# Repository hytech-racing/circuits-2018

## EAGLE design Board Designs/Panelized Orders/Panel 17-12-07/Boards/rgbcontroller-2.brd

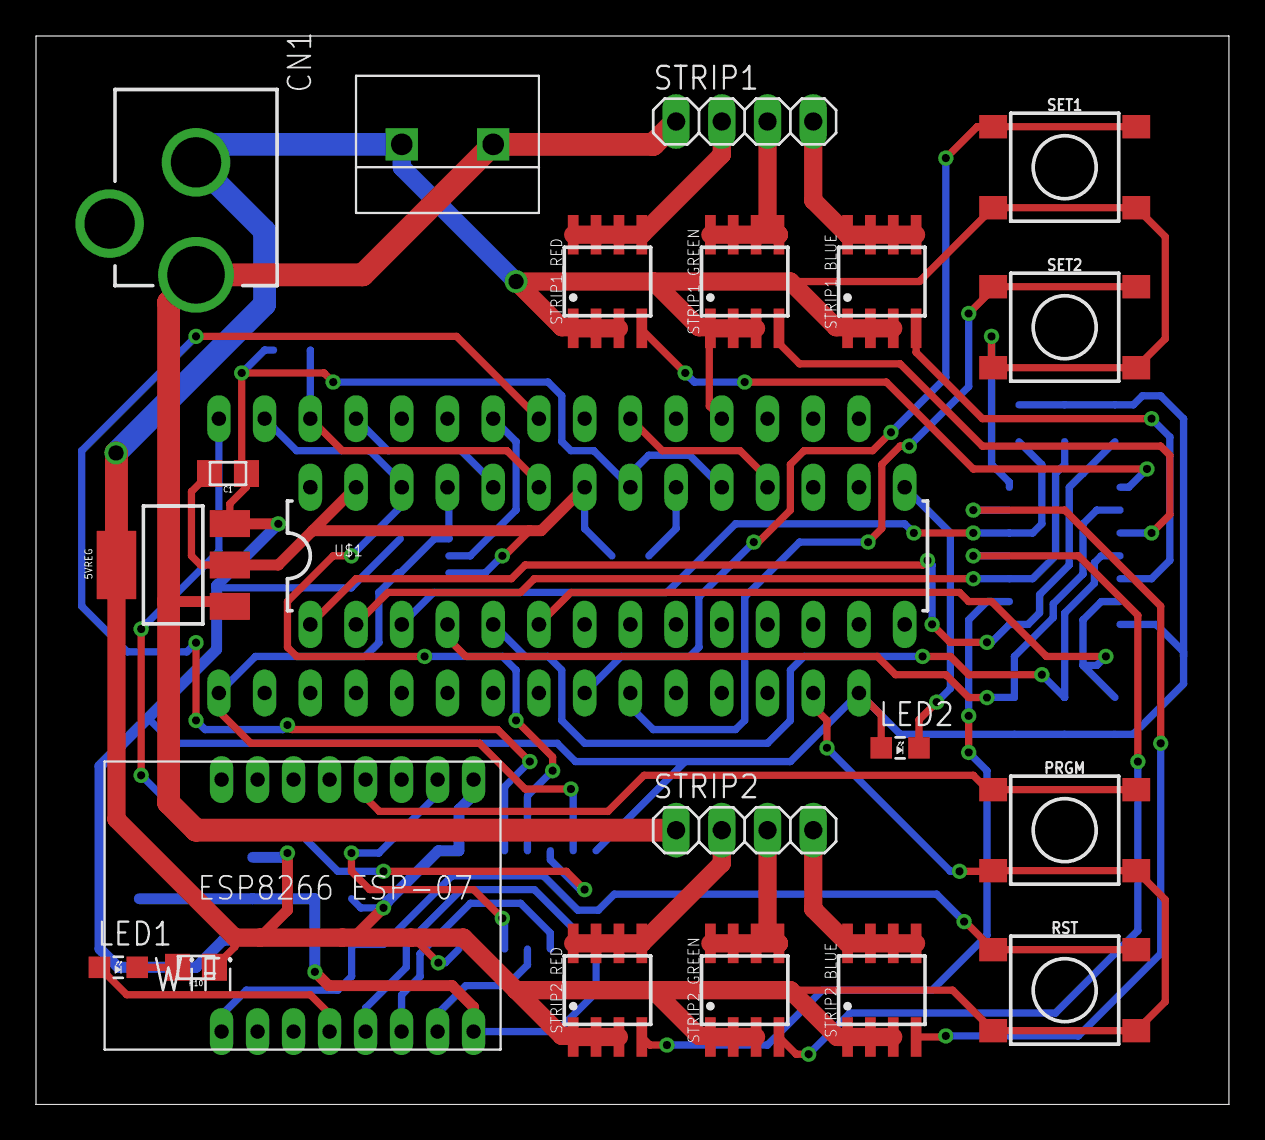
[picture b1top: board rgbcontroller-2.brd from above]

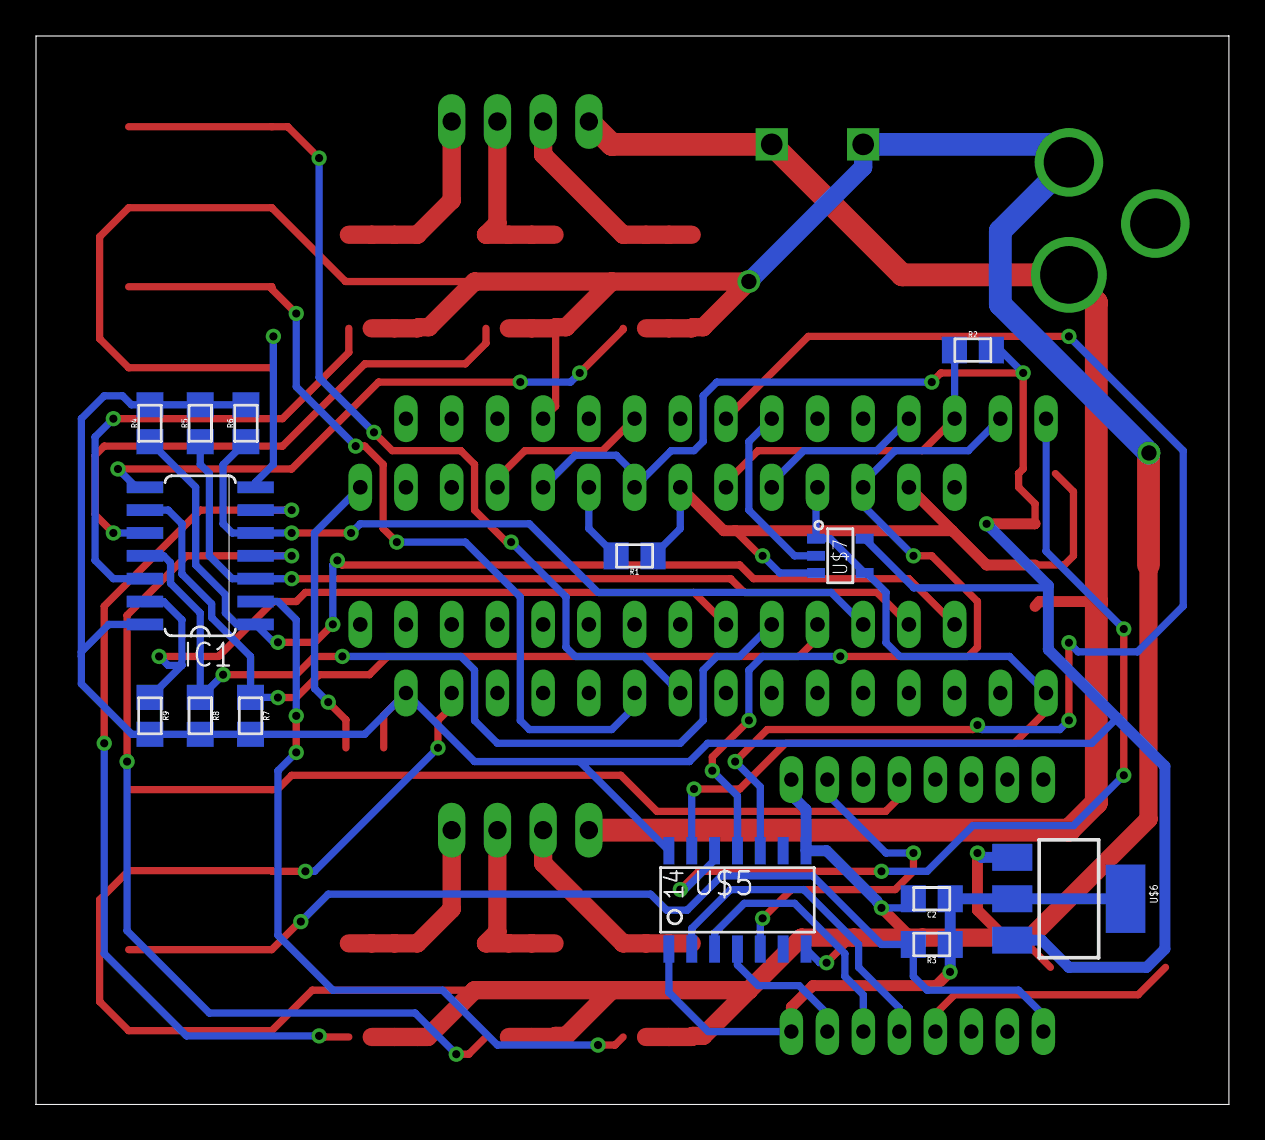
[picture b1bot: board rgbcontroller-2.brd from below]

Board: 2 copper layers, 66.3 x 59.4 mm, 36 parts (14 on the bottom side), 42 nets.

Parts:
5VREG: SOT223
C1: .1µF; 0805
C2: 1µF; 0805
CN1: DCJACK_2MM_PTH
IC1: 74HC04D; SO14
LED1: Red; LED-805
LED2: LED-805
PRGM: TACTILE_SWITCH_SMD_6.2MM_TALL
R1: 2.2k; 0805
R2, R3, R4, R5, R6, R7, R8, R9: 10k; 0805
R10: 100; 0805
RST: TACTILE_SWITCH_SMD_6.2MM_TALL
SET1, SET2: TACTILE_SWITCH_SMD_6.2MM_TALL
STRIP1, STRIP2: 1X04
STRIP1_BLUE, STRIP1_GREEN, STRIP1_RED, STRIP2_BLUE, STRIP2_GREEN, STRIP2_RED: MDS1656; SOIC-08
U$1: TLC5940; DIL28-3
U$2: ARDUINO_NANO
U$3: TERMINAL_BLOCK_DG301-02P; DG301-02P
U$4: ESP8266_ESP-07
U$5: SOIC-14
U$6: TLV1117LV33; SOT223
U$7: SN74LVC1G08; SOT-23-5

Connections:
+3V3: C2.1, R3.1, U$4.P$8, U$5.1, U$6.2, U$6.4
+5V: 5VREG.3, C1.1, IC1.14, LED2.A, R2.2, R4.2, R5.2, R6.2, R7.2, R8.2, R9.2, U$1.19, U$1.21, U$2.VIN, U$5.14, U$6.3, U$7.5
+12V: 5VREG.1, CN1.PWR, STRIP1.1, STRIP2.1, U$3.1
BLANK: R2.1, U$1.23, U$2.D10
GND: 5VREG.2, 5VREG.4, C1.2, C2.2, CN1.GND, IC1.7, PRGM.A1, PRGM.A2, R1.1, R10.1, RST.A1, RST.A2, SET1.A1, SET1.A2, SET2.A1, SET2.A2, STRIP1_BLUE.1, STRIP1_BLUE.2, STRIP1_BLUE.3, STRIP1_GREEN.1, STRIP1_GREEN.2, STRIP1_GREEN.3, STRIP1_RED.1, STRIP1_RED.2, STRIP1_RED.3, STRIP2_BLUE.1, STRIP2_BLUE.2, STRIP2_BLUE.3, STRIP2_GREEN.1, STRIP2_GREEN.2, STRIP2_GREEN.3, STRIP2_RED.1, STRIP2_RED.2, STRIP2_RED.3, U$1.22, U$1.27, U$2.GND, U$2.GND1, U$3.2, U$4.P$9, U$5.7, U$5.8, U$6.1, U$7.3
MISO: U$2.D12, U$5.12
MISO_33: U$4.P$6, U$5.3
MOSI: U$1.26, U$2.D11, U$5.11
MOSI_33: U$4.P$7, U$5.4
unnamed: STRIP2.2, STRIP2_RED.5, STRIP2_RED.6, STRIP2_RED.7, STRIP2_RED.8
unnamed: STRIP1.2, STRIP1_RED.5, STRIP1_RED.6, STRIP1_RED.7, STRIP1_RED.8
unnamed: IC1.2, STRIP2_RED.4
unnamed: IC1.4, STRIP2_GREEN.4
unnamed: PRGM.B1, PRGM.B2, U$4.P$12
unnamed: R1.2, U$1.20
unnamed: U$1.18, U$2.D3
unnamed: LED1.A, U$4.P$4
unnamed: IC1.8, STRIP1_RED.4
unnamed: IC1.10, STRIP1_GREEN.4
unnamed: IC1.12, STRIP1_BLUE.4
unnamed: IC1.6, STRIP2_BLUE.4
unnamed: IC1.1, R4.1, U$1.1
unnamed: IC1.3, R5.1, U$1.2
unnamed: STRIP1.3, STRIP1_GREEN.5, STRIP1_GREEN.6, STRIP1_GREEN.7, STRIP1_GREEN.8
unnamed: STRIP1.4, STRIP1_BLUE.5, STRIP1_BLUE.6, STRIP1_BLUE.7, STRIP1_BLUE.8
unnamed: STRIP2.3, STRIP2_GREEN.5, STRIP2_GREEN.6, STRIP2_GREEN.7, STRIP2_GREEN.8
unnamed: STRIP2.4, STRIP2_BLUE.5, STRIP2_BLUE.6, STRIP2_BLUE.7, STRIP2_BLUE.8
unnamed: IC1.5, R6.1, U$1.3
unnamed: IC1.13, R9.1, U$1.6
unnamed: R3.2, RST.B1, RST.B2, U$4.P$1
unnamed: IC1.11, R8.1, U$1.5
unnamed: IC1.9, R7.1, U$1.4
unnamed: LED2.C, U$1.15
unnamed: LED1.C, R10.2
SCK: U$1.25, U$2.D13, U$5.13, U$7.1, U$7.4
SCK_33: U$4.P$5, U$5.2
SET1: SET1.B1, SET1.B2, U$2.A5
SET2: SET2.B1, SET2.B2, U$2.A6
SS_ESP8266: U$2.D5, U$5.10
SS_ESP8266_33: U$4.P$10, U$5.5
SS_TLC5940: U$2.D6, U$7.2
XLAT: U$1.24, U$2.D9

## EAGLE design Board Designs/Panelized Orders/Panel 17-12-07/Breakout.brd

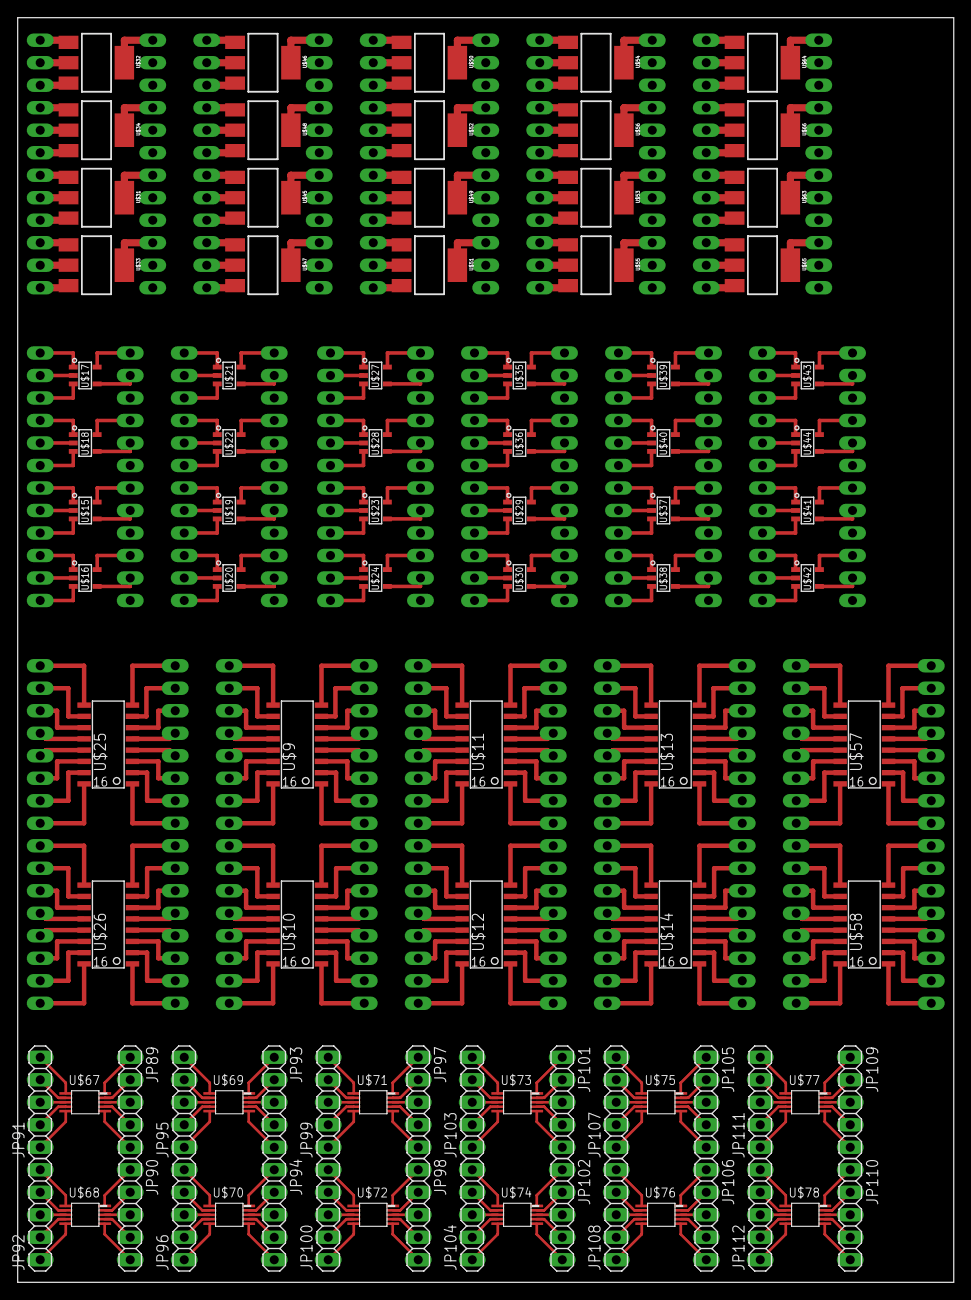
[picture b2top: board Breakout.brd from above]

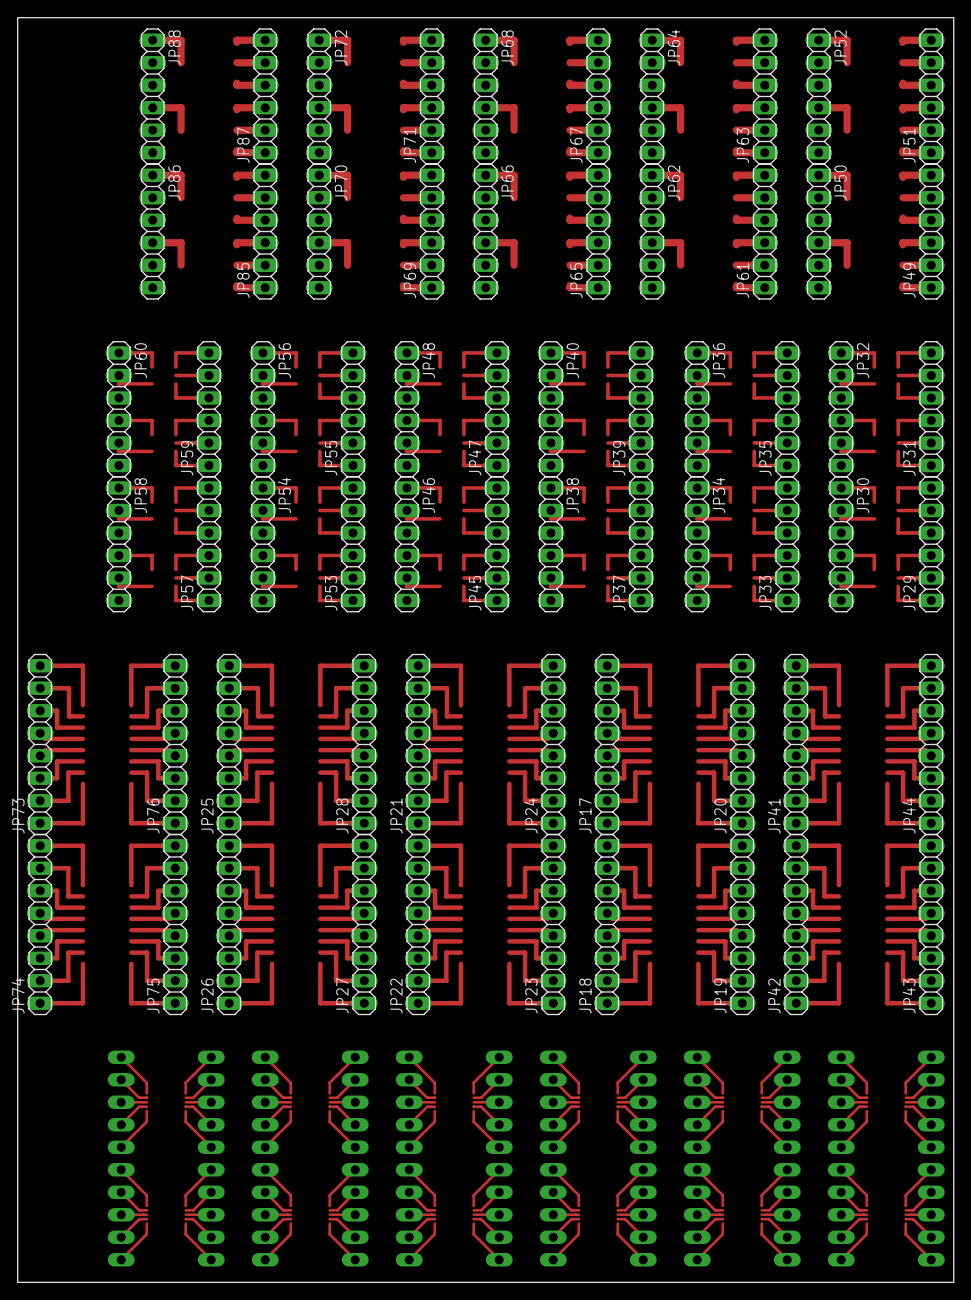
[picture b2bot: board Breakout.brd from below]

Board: 2 copper layers, 105.7 x 142.7 mm, 154 parts (64 on the bottom side), 480 nets.

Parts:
JP17, JP18, JP19, JP20, JP21, JP22, JP23, JP24, JP25, JP26, JP27, JP28, JP41, JP42, JP43, JP44, JP73, JP74, JP75, JP76: 1X08
JP29, JP30, JP31, JP32, JP33, JP34, JP35, JP36, JP37, JP38, JP39, JP40, JP45, JP46, JP47, JP48, JP49, JP50, JP51, JP52, JP53, JP54, JP55, JP56, JP57, JP58, JP59, JP60, JP61, JP62, JP63, JP64, JP65, JP66, JP67, JP68, JP69, JP70, JP71, JP72, JP85, JP86, JP87, JP88: 1X06
JP89, JP90, JP91, JP92, JP93, JP94, JP95, JP96, JP97, JP98, JP99, JP100, JP101, JP102, JP103, JP104, JP105, JP106, JP107, JP108, JP109, JP110, JP111, JP112: 1X05
U$9, U$10, U$11, U$12, U$13, U$14, U$25, U$26, U$57, U$58: SOIC16; SOIC-16
U$15, U$17, U$19, U$21, U$23, U$27, U$29, U$35, U$37, U$39, U$41, U$43: SN74LVC1G06; SOT-23-5
U$16, U$18, U$20, U$22, U$24, U$28, U$30, U$36, U$38, U$40, U$42, U$44: SN74LVC1G07; SOT-23-5
U$31, U$32, U$33, U$34, U$45, U$46, U$47, U$48, U$49, U$50, U$51, U$52, U$53, U$54, U$55, U$56, U$63, U$64, U$65, U$66: SOT223
U$67, U$68, U$69, U$70, U$71, U$72, U$73, U$74, U$75, U$76, U$77, U$78: INA226; VSSOP-10

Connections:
unnamed: JP17.1, U$9.1
unnamed: JP17.2, U$9.2
unnamed: JP17.3, U$9.3
unnamed: JP17.4, U$9.4
unnamed: JP17.5, U$9.5
unnamed: JP17.6, U$9.6
unnamed: JP17.7, U$9.7
unnamed: JP17.8, U$9.8
unnamed: JP18.1, U$10.1
unnamed: JP18.2, U$10.2
unnamed: JP18.3, U$10.3
unnamed: JP18.4, U$10.4
unnamed: JP18.5, U$10.5
unnamed: JP18.6, U$10.6
unnamed: JP18.7, U$10.7
unnamed: JP18.8, U$10.8
unnamed: JP19.1, U$10.16
unnamed: JP19.2, U$10.15
unnamed: JP19.3, U$10.14
unnamed: JP19.4, U$10.13
unnamed: JP19.5, U$10.12
unnamed: JP19.6, U$10.11
unnamed: JP19.7, U$10.10
unnamed: JP19.8, U$10.9
unnamed: JP20.1, U$9.16
unnamed: JP20.2, U$9.15
unnamed: JP20.3, U$9.14
unnamed: JP20.4, U$9.13
unnamed: JP20.5, U$9.12
unnamed: JP20.6, U$9.11
unnamed: JP20.7, U$9.10
unnamed: JP20.8, U$9.9
unnamed: JP21.1, U$11.1
unnamed: JP21.2, U$11.2
unnamed: JP21.3, U$11.3
unnamed: JP21.4, U$11.4
unnamed: JP21.5, U$11.5
unnamed: JP21.6, U$11.6
unnamed: JP21.7, U$11.7
unnamed: JP21.8, U$11.8
unnamed: JP22.1, U$12.1
unnamed: JP22.2, U$12.2
unnamed: JP22.3, U$12.3
unnamed: JP22.4, U$12.4
unnamed: JP22.5, U$12.5
unnamed: JP22.6, U$12.6
unnamed: JP22.7, U$12.7
unnamed: JP22.8, U$12.8
unnamed: JP23.1, U$12.16
unnamed: JP23.2, U$12.15
unnamed: JP23.3, U$12.14
unnamed: JP23.4, U$12.13
unnamed: JP23.5, U$12.12
unnamed: JP23.6, U$12.11
unnamed: JP23.7, U$12.10
unnamed: JP23.8, U$12.9
unnamed: JP24.1, U$11.16
unnamed: JP24.2, U$11.15
unnamed: JP24.3, U$11.14
unnamed: JP24.4, U$11.13
unnamed: JP24.5, U$11.12
unnamed: JP24.6, U$11.11
unnamed: JP24.7, U$11.10
unnamed: JP24.8, U$11.9
unnamed: JP25.1, U$13.1
unnamed: JP25.2, U$13.2
unnamed: JP25.3, U$13.3
unnamed: JP25.4, U$13.4
unnamed: JP25.5, U$13.5
unnamed: JP25.6, U$13.6
unnamed: JP25.7, U$13.7
unnamed: JP25.8, U$13.8
unnamed: JP26.1, U$14.1
unnamed: JP26.2, U$14.2
unnamed: JP26.3, U$14.3
unnamed: JP26.4, U$14.4
unnamed: JP26.5, U$14.5
unnamed: JP26.6, U$14.6
unnamed: JP26.7, U$14.7
unnamed: JP26.8, U$14.8
unnamed: JP27.1, U$14.16
unnamed: JP27.2, U$14.15
unnamed: JP27.3, U$14.14
unnamed: JP27.4, U$14.13
unnamed: JP27.5, U$14.12
unnamed: JP27.6, U$14.11
unnamed: JP27.7, U$14.10
unnamed: JP27.8, U$14.9
unnamed: JP28.1, U$13.16
unnamed: JP28.2, U$13.15
unnamed: JP28.3, U$13.14
unnamed: JP28.4, U$13.13
unnamed: JP28.5, U$13.12
unnamed: JP28.6, U$13.11
unnamed: JP28.7, U$13.10
unnamed: JP28.8, U$13.9
unnamed: JP30.1, U$15.5
unnamed: JP30.2, U$15.4
unnamed: JP30.4, U$16.5
unnamed: JP30.5, U$16.4
unnamed: JP29.6, U$15.1
unnamed: JP29.5, U$15.2
unnamed: JP29.4, U$15.3
unnamed: JP29.3, U$16.1
unnamed: JP29.2, U$16.2
unnamed: JP29.1, U$16.3
unnamed: JP32.1, U$17.5
unnamed: JP32.2, U$17.4
unnamed: JP32.4, U$18.5
unnamed: JP32.5, U$18.4
unnamed: JP31.6, U$17.1
unnamed: JP31.5, U$17.2
unnamed: JP31.4, U$17.3
unnamed: JP31.3, U$18.1
unnamed: JP31.2, U$18.2
unnamed: JP31.1, U$18.3
unnamed: JP34.1, U$19.5
unnamed: JP34.2, U$19.4
unnamed: JP34.4, U$20.5
unnamed: JP34.5, U$20.4
unnamed: JP33.6, U$19.1
unnamed: JP33.5, U$19.2
unnamed: JP33.4, U$19.3
unnamed: JP33.3, U$20.1
unnamed: JP33.2, U$20.2
unnamed: JP33.1, U$20.3
unnamed: JP36.1, U$21.5
unnamed: JP36.2, U$21.4
unnamed: JP36.4, U$22.5
unnamed: JP36.5, U$22.4
unnamed: JP35.6, U$21.1
unnamed: JP35.5, U$21.2
unnamed: JP35.4, U$21.3
unnamed: JP35.3, U$22.1
unnamed: JP35.2, U$22.2
unnamed: JP35.1, U$22.3
unnamed: JP38.1, U$23.5
unnamed: JP38.2, U$23.4
unnamed: JP38.4, U$24.5
unnamed: JP38.5, U$24.4
unnamed: JP37.6, U$23.1
unnamed: JP37.5, U$23.2
unnamed: JP37.4, U$23.3
unnamed: JP37.3, U$24.1
unnamed: JP37.2, U$24.2
unnamed: JP37.1, U$24.3
unnamed: JP40.1, U$27.5
unnamed: JP40.2, U$27.4
unnamed: JP40.4, U$28.5
unnamed: JP40.5, U$28.4
unnamed: JP39.6, U$27.1
unnamed: JP39.5, U$27.2
unnamed: JP39.4, U$27.3
unnamed: JP39.3, U$28.1
unnamed: JP39.2, U$28.2
unnamed: JP39.1, U$28.3
unnamed: JP46.1, U$29.5
unnamed: JP46.2, U$29.4
unnamed: JP46.4, U$30.5
unnamed: JP46.5, U$30.4
unnamed: JP45.6, U$29.1
unnamed: JP45.5, U$29.2
unnamed: JP45.4, U$29.3
unnamed: JP45.3, U$30.1
unnamed: JP41.1, U$25.1
unnamed: JP41.2, U$25.2
unnamed: JP41.3, U$25.3
unnamed: JP41.4, U$25.4
unnamed: JP41.5, U$25.5
unnamed: JP41.6, U$25.6
unnamed: JP41.7, U$25.7
unnamed: JP41.8, U$25.8
unnamed: JP42.1, U$26.1
unnamed: JP42.2, U$26.2
unnamed: JP42.3, U$26.3
unnamed: JP42.4, U$26.4
unnamed: JP42.5, U$26.5
unnamed: JP42.6, U$26.6
unnamed: JP42.7, U$26.7
unnamed: JP42.8, U$26.8
unnamed: JP43.1, U$26.16
unnamed: JP43.2, U$26.15
unnamed: JP43.3, U$26.14
unnamed: JP43.4, U$26.13
unnamed: JP43.5, U$26.12
unnamed: JP43.6, U$26.11
unnamed: JP43.7, U$26.10
unnamed: JP43.8, U$26.9
unnamed: JP44.1, U$25.16
unnamed: JP44.2, U$25.15
unnamed: JP44.3, U$25.14
unnamed: JP44.4, U$25.13
unnamed: JP44.5, U$25.12
unnamed: JP44.6, U$25.11
unnamed: JP44.7, U$25.10
unnamed: JP44.8, U$25.9
unnamed: JP45.2, U$30.2
unnamed: JP45.1, U$30.3
unnamed: JP48.1, U$35.5
unnamed: JP48.2, U$35.4
unnamed: JP48.4, U$36.5
unnamed: JP48.5, U$36.4
unnamed: JP47.6, U$35.1
unnamed: JP47.5, U$35.2
unnamed: JP47.4, U$35.3
unnamed: JP47.3, U$36.1
unnamed: JP47.2, U$36.2
unnamed: JP47.1, U$36.3
unnamed: JP54.1, U$37.5
unnamed: JP54.2, U$37.4
unnamed: JP54.4, U$38.5
unnamed: JP54.5, U$38.4
unnamed: JP53.6, U$37.1
unnamed: JP53.5, U$37.2
unnamed: JP53.4, U$37.3
unnamed: JP53.3, U$38.1
unnamed: JP50.1, U$31.4
unnamed: JP49.6, U$31.1
unnamed: JP49.5, U$31.2
unnamed: JP49.4, U$31.3
unnamed: JP49.3, U$33.1
unnamed: JP49.2, U$33.2
unnamed: JP49.1, U$33.3
unnamed: JP50.4, U$33.4
unnamed: JP52.1, U$32.4
unnamed: JP52.4, U$34.4
unnamed: JP51.6, U$32.1
unnamed: JP51.5, U$32.2
unnamed: JP51.4, U$32.3
unnamed: JP51.3, U$34.1
unnamed: JP51.2, U$34.2
unnamed: JP51.1, U$34.3
unnamed: JP53.2, U$38.2
unnamed: JP53.1, U$38.3
unnamed: JP56.1, U$39.5
unnamed: JP56.2, U$39.4
unnamed: JP56.4, U$40.5
unnamed: JP56.5, U$40.4
unnamed: JP55.6, U$39.1
unnamed: JP55.5, U$39.2
unnamed: JP55.4, U$39.3
unnamed: JP55.3, U$40.1
unnamed: JP55.2, U$40.2
unnamed: JP55.1, U$40.3
unnamed: JP58.1, U$41.5
unnamed: JP58.2, U$41.4
unnamed: JP58.4, U$42.5
unnamed: JP58.5, U$42.4
unnamed: JP57.6, U$41.1
unnamed: JP57.5, U$41.2
unnamed: JP57.4, U$41.3
unnamed: JP57.3, U$42.1
unnamed: JP57.2, U$42.2
unnamed: JP57.1, U$42.3
unnamed: JP60.1, U$43.5
unnamed: JP60.2, U$43.4
unnamed: JP60.4, U$44.5
unnamed: JP60.5, U$44.4
unnamed: JP59.6, U$43.1
unnamed: JP59.5, U$43.2
unnamed: JP59.4, U$43.3
unnamed: JP59.3, U$44.1
unnamed: JP59.2, U$44.2
unnamed: JP59.1, U$44.3
unnamed: JP62.1, U$45.4
unnamed: JP61.6, U$45.1
unnamed: JP61.5, U$45.2
unnamed: JP61.4, U$45.3
unnamed: JP61.3, U$47.1
unnamed: JP61.2, U$47.2
unnamed: JP61.1, U$47.3
unnamed: JP62.4, U$47.4
unnamed: JP64.1, U$46.4
unnamed: JP64.4, U$48.4
unnamed: JP63.6, U$46.1
unnamed: JP63.5, U$46.2
unnamed: JP63.4, U$46.3
unnamed: JP63.3, U$48.1
unnamed: JP63.2, U$48.2
unnamed: JP63.1, U$48.3
unnamed: JP66.1, U$49.4
unnamed: JP65.6, U$49.1
unnamed: JP65.5, U$49.2
unnamed: JP65.4, U$49.3
unnamed: JP65.3, U$51.1
unnamed: JP65.2, U$51.2
unnamed: JP65.1, U$51.3
unnamed: JP66.4, U$51.4
unnamed: JP68.1, U$50.4
unnamed: JP68.4, U$52.4
unnamed: JP67.6, U$50.1
unnamed: JP67.5, U$50.2
unnamed: JP67.4, U$50.3
unnamed: JP67.3, U$52.1
unnamed: JP67.2, U$52.2
unnamed: JP67.1, U$52.3
unnamed: JP70.1, U$53.4
unnamed: JP69.6, U$53.1
unnamed: JP69.5, U$53.2
unnamed: JP69.4, U$53.3
unnamed: JP69.3, U$55.1
unnamed: JP69.2, U$55.2
unnamed: JP69.1, U$55.3
unnamed: JP70.4, U$55.4
unnamed: JP72.1, U$54.4
unnamed: JP72.4, U$56.4
unnamed: JP71.6, U$54.1
unnamed: JP71.5, U$54.2
unnamed: JP71.4, U$54.3
unnamed: JP71.3, U$56.1
unnamed: JP71.2, U$56.2
unnamed: JP71.1, U$56.3
unnamed: JP73.1, U$57.1
unnamed: JP73.2, U$57.2
unnamed: JP73.3, U$57.3
unnamed: JP73.4, U$57.4
unnamed: JP73.5, U$57.5
unnamed: JP73.6, U$57.6
unnamed: JP73.7, U$57.7
unnamed: JP73.8, U$57.8
unnamed: JP74.1, U$58.1
unnamed: JP74.2, U$58.2
unnamed: JP74.3, U$58.3
unnamed: JP74.4, U$58.4
unnamed: JP74.5, U$58.5
unnamed: JP74.6, U$58.6
unnamed: JP74.7, U$58.7
unnamed: JP74.8, U$58.8
unnamed: JP75.1, U$58.16
unnamed: JP75.2, U$58.15
unnamed: JP75.3, U$58.14
unnamed: JP75.4, U$58.13
unnamed: JP75.5, U$58.12
unnamed: JP75.6, U$58.11
unnamed: JP75.7, U$58.10
unnamed: JP75.8, U$58.9
unnamed: JP76.1, U$57.16
unnamed: JP76.2, U$57.15
unnamed: JP76.3, U$57.14
unnamed: JP76.4, U$57.13
unnamed: JP76.5, U$57.12
unnamed: JP76.6, U$57.11
unnamed: JP76.7, U$57.10
unnamed: JP76.8, U$57.9
unnamed: JP86.1, U$63.4
unnamed: JP85.6, U$63.1
unnamed: JP85.5, U$63.2
unnamed: JP85.4, U$63.3
unnamed: JP85.3, U$65.1
unnamed: JP85.2, U$65.2
unnamed: JP85.1, U$65.3
unnamed: JP86.4, U$65.4
unnamed: JP88.1, U$64.4
unnamed: JP88.4, U$66.4
unnamed: JP87.6, U$64.1
unnamed: JP87.5, U$64.2
unnamed: JP87.4, U$64.3
unnamed: JP87.3, U$66.1
unnamed: JP87.2, U$66.2
unnamed: JP87.1, U$66.3
unnamed: JP92.1, U$68.5
unnamed: JP92.2, U$68.4
unnamed: JP92.3, U$68.3
unnamed: JP92.4, U$68.2
unnamed: JP92.5, U$68.1
unnamed: JP91.1, U$67.5
unnamed: JP91.2, U$67.4
unnamed: JP91.3, U$67.3
unnamed: JP91.4, U$67.2
unnamed: JP91.5, U$67.1
unnamed: JP90.1, U$68.10
unnamed: JP90.2, U$68.9
unnamed: JP90.3, U$68.8
unnamed: JP90.4, U$68.7
unnamed: JP90.5, U$68.6
unnamed: JP89.1, U$67.10
unnamed: JP89.2, U$67.9
unnamed: JP89.3, U$67.8
unnamed: JP89.4, U$67.7
unnamed: JP89.5, U$67.6
unnamed: JP96.1, U$70.5
unnamed: JP96.2, U$70.4
unnamed: JP96.3, U$70.3
unnamed: JP96.4, U$70.2
unnamed: JP96.5, U$70.1
unnamed: JP95.1, U$69.5
unnamed: JP95.2, U$69.4
unnamed: JP95.3, U$69.3
unnamed: JP95.4, U$69.2
unnamed: JP95.5, U$69.1
unnamed: JP94.1, U$70.10
unnamed: JP94.2, U$70.9
unnamed: JP94.3, U$70.8
unnamed: JP94.4, U$70.7
unnamed: JP94.5, U$70.6
unnamed: JP93.1, U$69.10
unnamed: JP93.2, U$69.9
unnamed: JP93.3, U$69.8
unnamed: JP93.4, U$69.7
unnamed: JP93.5, U$69.6
unnamed: JP100.1, U$72.5
unnamed: JP100.2, U$72.4
unnamed: JP100.3, U$72.3
unnamed: JP100.4, U$72.2
unnamed: JP100.5, U$72.1
unnamed: JP99.1, U$71.5
unnamed: JP99.2, U$71.4
unnamed: JP99.3, U$71.3
unnamed: JP99.4, U$71.2
unnamed: JP99.5, U$71.1
unnamed: JP98.1, U$72.10
unnamed: JP98.2, U$72.9
unnamed: JP98.3, U$72.8
unnamed: JP98.4, U$72.7
unnamed: JP98.5, U$72.6
unnamed: JP97.1, U$71.10
unnamed: JP97.2, U$71.9
unnamed: JP97.3, U$71.8
unnamed: JP97.4, U$71.7
unnamed: JP97.5, U$71.6
unnamed: JP104.1, U$74.5
unnamed: JP104.2, U$74.4
unnamed: JP104.3, U$74.3
unnamed: JP104.4, U$74.2
unnamed: JP104.5, U$74.1
unnamed: JP103.1, U$73.5
unnamed: JP103.2, U$73.4
unnamed: JP103.3, U$73.3
unnamed: JP103.4, U$73.2
unnamed: JP103.5, U$73.1
unnamed: JP102.1, U$74.10
unnamed: JP102.2, U$74.9
unnamed: JP102.3, U$74.8
unnamed: JP102.4, U$74.7
unnamed: JP102.5, U$74.6
unnamed: JP101.1, U$73.10
unnamed: JP101.2, U$73.9
unnamed: JP101.3, U$73.8
unnamed: JP101.4, U$73.7
unnamed: JP101.5, U$73.6
unnamed: JP108.1, U$76.5
unnamed: JP108.2, U$76.4
unnamed: JP108.3, U$76.3
unnamed: JP108.4, U$76.2
unnamed: JP108.5, U$76.1
unnamed: JP107.1, U$75.5
unnamed: JP107.2, U$75.4
unnamed: JP107.3, U$75.3
unnamed: JP107.4, U$75.2
unnamed: JP107.5, U$75.1
unnamed: JP106.1, U$76.10
unnamed: JP106.2, U$76.9
unnamed: JP106.3, U$76.8
unnamed: JP106.4, U$76.7
unnamed: JP106.5, U$76.6
unnamed: JP105.1, U$75.10
unnamed: JP105.2, U$75.9
unnamed: JP105.3, U$75.8
unnamed: JP105.4, U$75.7
unnamed: JP105.5, U$75.6
unnamed: JP112.1, U$78.5
unnamed: JP112.2, U$78.4
unnamed: JP112.3, U$78.3
unnamed: JP112.4, U$78.2
unnamed: JP112.5, U$78.1
unnamed: JP111.1, U$77.5
unnamed: JP111.2, U$77.4
unnamed: JP111.3, U$77.3
unnamed: JP111.4, U$77.2
unnamed: JP111.5, U$77.1
unnamed: JP110.1, U$78.10
unnamed: JP110.2, U$78.9
unnamed: JP110.3, U$78.8
unnamed: JP110.4, U$78.7
unnamed: JP110.5, U$78.6
unnamed: JP109.1, U$77.10
unnamed: JP109.2, U$77.9
unnamed: JP109.3, U$77.8
unnamed: JP109.4, U$77.7
unnamed: JP109.5, U$77.6

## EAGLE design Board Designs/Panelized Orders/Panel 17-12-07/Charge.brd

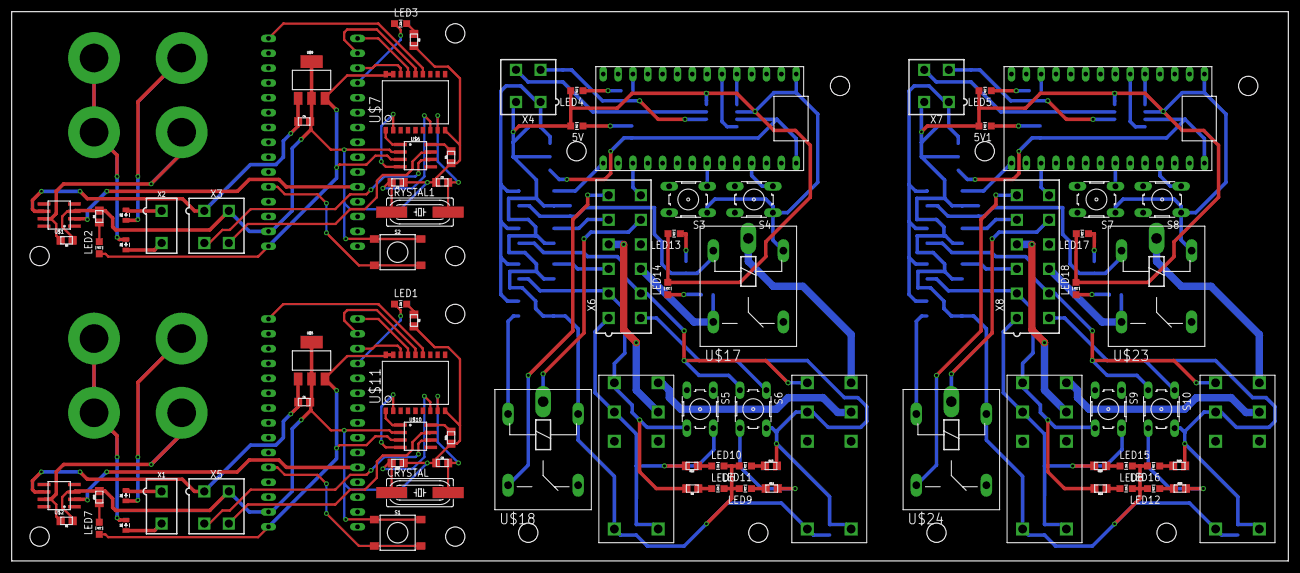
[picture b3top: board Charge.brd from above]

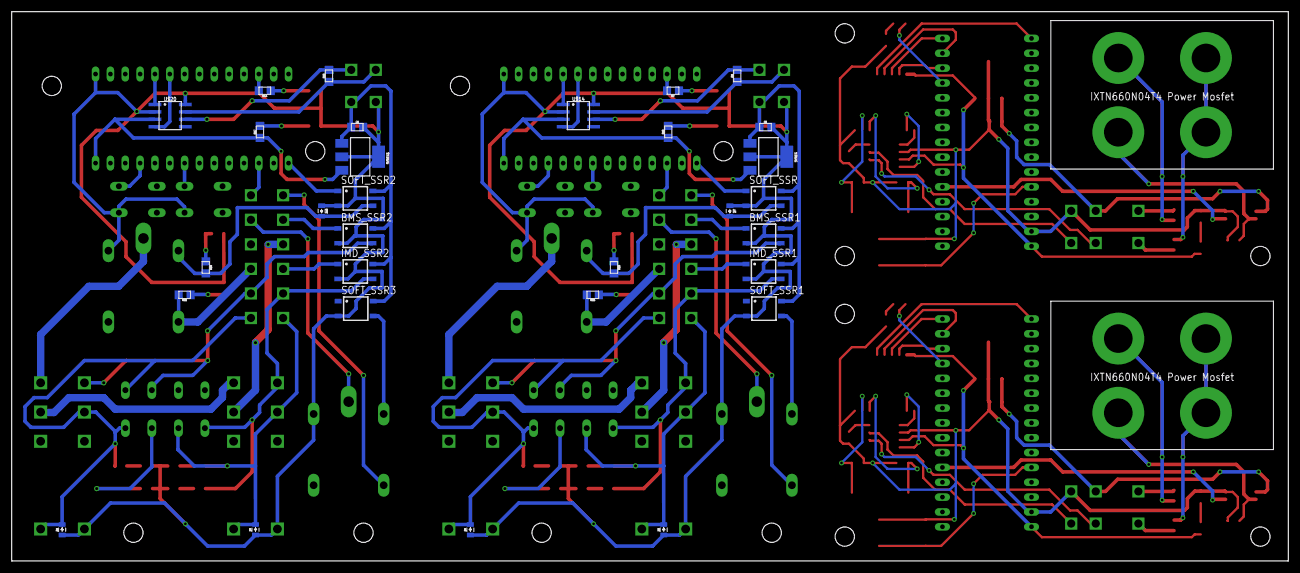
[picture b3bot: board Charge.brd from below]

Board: 2 copper layers, 218.4 x 94.0 mm, 118 parts (32 on the bottom side), 116 nets.

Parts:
5V, 5V1: LED-805
5VREG, 5VREG1: SOT223
BMS_SSR1, BMS_SSR2: CPC1002N; SOP04
C1, C4, C5, C6: .22uF; 0805
C2, C3, C9, C10: 22pF; 0805
CRYSTAL, CRYSTAL1: 16MHz; HC49UP
D1, D2, D3, D4, D5, D6, D7, D8, D9, D10: DIODE0805; 0805_D
IMD_SSR1, IMD_SSR2: CPC1002N; SOP04
LED1, LED3: GREEN; LED-805
LED2, LED7: PURPLE; LED-805
LED4, LED5, LED6, LED8, LED9, LED10, LED11, LED12, LED13, LED14, LED15, LED16, LED17, LED18: LED-805
R1, R3: 10k; 0805
R2, R5, R6, R28: 200; 0805
R4, R24: 4.7k; 0805
R7, R8, R10, R11, R12, R13, R14, R15, R16, R17, R18, R19, R20, R21, R22, R23: 0805
R9, R25: 120; 0805
S1, S2: TACTILE_SWITCH_SMD_6.2MM_TALL
S3, S4, S5, S6, S7, S8, S9, S10: B3F-10XX
SOFT_SSR, SOFT_SSR1, SOFT_SSR2, SOFT_SSR3: CPC1002N; SOP04
U$1, U$2: MC34152; SOIC-08
U$3, U$12: IXTN660N04T4; SOT-227B
U$4, U$8: ARDUINO_NANO
U$5, U$9: SOT223
U$6, U$10, U$14, U$20: MCP2551; SOIC-08
U$7, U$11: MCP2515SMD; SOIC-18W
U$13, U$19: TEENSY_3.2_SIMPLE
U$15, U$16, U$21, U$22: G2RL-2-DC12; G2RL-2
U$17, U$18, U$23, U$24: G5LE; ZF112
X1, X2: CONNECTOR-2; MINIFIT_5566-2
X3, X5: MINIFIT_5566-4
X4, X7: CONNECTOR-4; MINIFIT_5566-4
X6, X8: CONNECTOR-12; MINIFIT_5566-12

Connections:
+5V: LED7.A, U$4.VIN, U$5.3, U$10.3, U$11.17, U$11.18
+5V1: LED2.A, U$6.3, U$7.17, U$7.18, U$8.VIN, U$9.3
+5V2: 5VREG.3, R10.1, U$13.VIN, U$14.3
+5V3: 5VREG1.3, R17.1, U$19.VIN, U$20.3
+12V: C1.1, U$2.6, U$5.1, X5.1
+12V1: C4.1, U$1.6, U$9.1, X3.1
+12V2: 5VREG.1, BMS_SSR1.4, C5.1, IMD_SSR1.4, SOFT_SSR.4, SOFT_SSR1.4, X4.1
+12V3: 5VREG1.1, BMS_SSR2.4, C6.1, IMD_SSR2.4, SOFT_SSR2.4, SOFT_SSR3.4, X7.1
BMS: BMS_SSR1.1, X6.5
BMS1: BMS_SSR2.1, X8.5
BMS_12V: BMS_SSR1.3, R11.2, S6.3, S6.4, U$16.4, X6.8
BMS_12V1: BMS_SSR2.3, R23.2, S10.3, S10.4, U$22.4, X8.8
BMS_OK: D6.C, R13.2, S6.1, S6.2, U$16.3, U$16.COIL-, X6.7
BMS_OK1: D9.C, R19.2, S10.1, S10.2, U$22.3, U$22.COIL-, X8.7
BTN_X: S4.3, U$13.A9
BTN_X1: S8.3, U$19.A9
BTN_Y: S3.3, U$13.A6
BTN_Y1: S7.3, U$19.A6
CANH: U$10.7, X5.4
CANH1: U$6.7, X3.4
CANH2: R9.1, U$14.7, X4.4
CANH3: R25.1, U$20.7, X7.4
CANL: U$10.6, X5.3
CANL1: U$6.6, X3.3
CANL2: R9.2, U$14.6, X4.3
CANL3: R25.2, U$20.6, X7.3
CANRX: U$13.D4(CANRX), U$14.4
CANRX1: U$19.D4(CANRX), U$20.4
CANTX: U$13.D3(CANTX), U$14.1
CANTX1: U$19.D3(CANTX), U$20.1
CS: U$4.D10, U$11.16
CS1: U$7.16, U$8.D10
GND: C1.2, C9.1, C10.1, R1.1, R2.2, R24.1, R28.2, S1.B1, S1.B2, U$2.3, U$4.GND, U$5.2, U$5.4, U$10.2, U$11.9, X5.2
GND1: C2.1, C3.1, C4.2, R3.1, R4.1, R5.2, R6.2, S2.B1, S2.B2, U$1.3, U$6.2, U$7.9, U$8.GND, U$9.2, U$9.4, X3.2
GND2: 5V.C, 5VREG.2, 5VREG.4, BMS_SSR1.2, C5.2, D5.A, D6.A, D7.A, IMD_SSR1.2, LED4.C, LED6.C, LED9.C, LED10.C, LED11.C, LED13.C, LED14.C, S3.1, S4.1, SOFT_SSR.2, SOFT_SSR1.2, U$13.GND, U$14.2, U$14.8, U$15.COIL+, U$16.COIL+, U$17.1, U$18.1, X4.2
GND3: 5V1.C, 5VREG1.2, 5VREG1.4, BMS_SSR2.2, C6.2, D8.A, D9.A, D10.A, IMD_SSR2.2, LED5.C, LED8.C, LED12.C, LED15.C, LED16.C, LED17.C, LED18.C, S7.1, S8.1, SOFT_SSR2.2, SOFT_SSR3.2, U$19.GND, U$20.2, U$20.8, U$21.COIL+, U$22.COIL+, U$23.1, U$24.1, X7.2
GPIO: U$13.A1, X6.12
GPIO1: U$19.A1, X8.12
IMD: IMD_SSR1.1, X6.3
IMD1: IMD_SSR2.1, X8.3
IMD_12V: IMD_SSR1.3, R8.2, S5.3, S5.4, U$15.4, X6.2
IMD_12V1: IMD_SSR2.3, R22.2, S9.3, S9.4, U$21.4, X8.2
IMD_OK: D5.C, R12.2, S5.1, S5.2, U$15.3, U$15.COIL-, X6.1
IMD_OK1: D8.C, R18.2, S9.1, S9.2, U$21.3, U$21.COIL-, X8.1
MISO: U$4.D12, U$11.15
MISO1: U$7.15, U$8.D12
MOSI: U$4.D11, U$11.14
MOSI1: U$7.14, U$8.D11
unnamed: D1.C, X1.1
unnamed: D1.A, U$3.P$1
unnamed: R1.2, U$2.7, U$3.P$4
unnamed: U$2.2, U$4.D2
unnamed: D2.C, U$3.P$2, U$3.P$3
unnamed: LED1.A, U$4.D9
unnamed: D2.A, X1.2
unnamed: LED1.C, R2.1
unnamed: S1.A1, S1.A2, U$4.A7
unnamed: R3.2, U$1.7, U$12.P$4
unnamed: D3.A, U$12.P$1
unnamed: U$1.2, U$8.D2
unnamed: D3.C, X2.1
unnamed: D4.C, U$12.P$2, U$12.P$3
unnamed: U$6.1, U$7.1
unnamed: U$6.4, U$7.2
unnamed: C2.2, CRYSTAL1.2, U$7.8
unnamed: R4.2, U$6.8
unnamed: C3.2, CRYSTAL1.1, U$7.7
unnamed: LED2.C, R5.1
unnamed: D4.A, X2.2
unnamed: LED3.C, R6.1
unnamed: LED3.A, U$8.D9
unnamed: S2.A1, S2.A2, U$8.A7
unnamed: LED6.A, R8.1
unnamed: LED10.A, R12.1
unnamed: LED11.A, R13.1
unnamed: LED13.A, R15.1
unnamed: LED14.A, R16.1
unnamed: LED9.A, R11.1
unnamed: SOFT_SSR1.3, U$18.2
unnamed: LED4.A, R7.1
unnamed: R7.2, U$13.D10(TX2)
unnamed: 5V.A, R10.2
unnamed: U$18.P, X6.11
unnamed: U$18.S, X6.6
unnamed: U$10.1, U$11.1
unnamed: LED8.A, R22.1
unnamed: U$10.4, U$11.2
unnamed: C9.2, CRYSTAL.2, U$11.8
unnamed: R24.2, U$10.8
unnamed: C10.2, CRYSTAL.1, U$11.7
unnamed: LED15.A, R18.1
unnamed: LED16.A, R19.1
unnamed: LED17.A, R20.1
unnamed: LED18.A, R21.1
unnamed: LED12.A, R23.1
unnamed: SOFT_SSR3.3, U$24.2
unnamed: LED5.A, R14.1
unnamed: R14.2, U$19.D10(TX2)
unnamed: 5V1.A, R17.2
unnamed: U$24.P, X8.11
unnamed: U$24.S, X8.6
unnamed: LED7.C, R28.1
SCK: U$4.D13, U$11.13
SCK1: U$7.13, U$8.D13
SHUTDOWN_IN: U$15.6, X6.4
SHUTDOWN_IN1: U$21.6, X8.4
SHUTDOWN_IN_A: U$15.5, U$16.6
SHUTDOWN_IN_A1: U$21.5, U$22.6
SHUTDOWN_IN_B: U$16.5, U$17.P
SHUTDOWN_IN_B1: U$22.5, U$23.P
SHUTDOWN_OUT: R16.2, U$17.S, X6.9
SHUTDOWN_OUT1: R21.2, U$23.S, X8.9
SW_KILL: SOFT_SSR.1, U$13.D13
SW_KILL1: SOFT_SSR2.1, U$19.D13
SW_KILL_RELAY: D7.C, R15.2, SOFT_SSR.3, U$17.2
SW_KILL_RELAY1: D10.C, R20.2, SOFT_SSR2.3, U$23.2

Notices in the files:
parts and their libraries:
SparkFun-FreqCtrl: Licensing: Creative Commons ShareAlike 4.0 International - https://creativecommons.org/licenses/by-sa/4.0
